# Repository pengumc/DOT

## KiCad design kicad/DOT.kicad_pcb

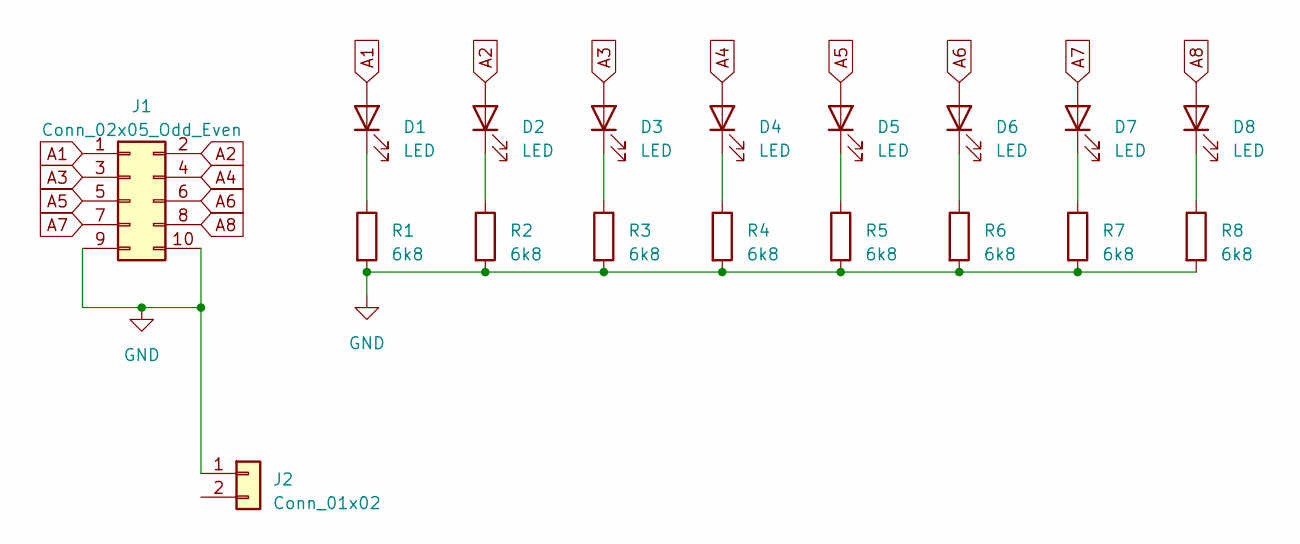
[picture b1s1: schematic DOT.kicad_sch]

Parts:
D1, D2, D3, D4, D5, D6, D7, D8: LED; LED_D5.0mm
J1: Conn_02x05_Odd_Even; IDC-Header_2x05_P2.54mm_Vertical
J2: Conn_01x02; TerminalBlock_Phoenix_MKDS-1,5-2-5.08_1x02_P5.08mm_Horizont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
R1, R2, R3, R4, R5, R6, R7, R8: 6k8; R_Axial_DIN0207_L6.3mm_D2.5mm_P10.16mm_Horizontal

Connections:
A1: D1.2 (A), J1.1
A2: D2.2 (A), J1.2
A3: D3.2 (A), J1.3
A4: D4.2 (A), J1.4
A5: D5.2 (A), J1.5
A6: D6.2 (A), J1.6
A7: D7.2 (A), J1.7
A8: D8.2 (A), J1.8
GND: J1.9, J1.10, J2.1, R1.2, R2.2, R3.2, R4.2, R5.2, R6.2, R7.2, R8.2
unnamed: D1.1 (K), R1.1
unnamed: D2.1 (K), R2.1
unnamed: D3.1 (K), R3.1
unnamed: D4.1 (K), R4.1
unnamed: D5.1 (K), R5.1
unnamed: D6.1 (K), R6.1
unnamed: D7.1 (K), R7.1
unnamed: D8.1 (K), R8.1

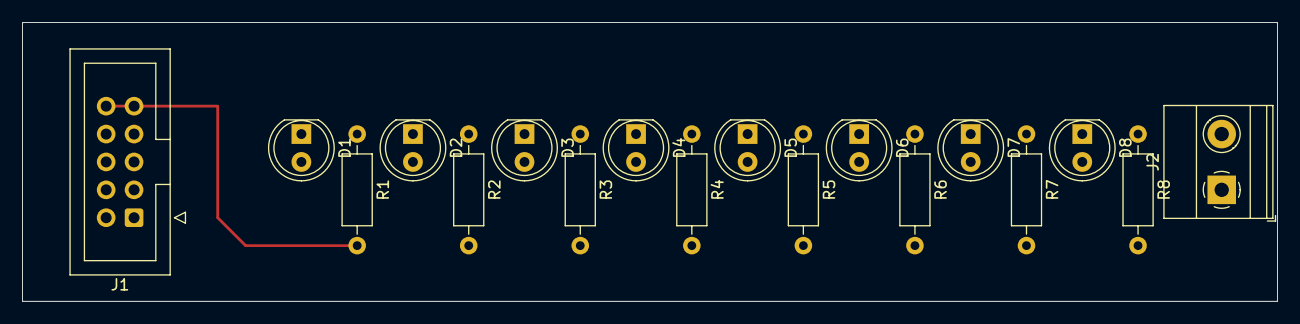
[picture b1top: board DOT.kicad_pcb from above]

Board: 2 copper layers, 114.3 x 25.4 mm, 18 parts (0 on the bottom side), 17 nets.

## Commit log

2023-06-04 Add freecad files
2023-11-24 Current files
